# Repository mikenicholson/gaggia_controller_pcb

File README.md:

gaggia_controller_pcb
=====================

A basic PID controller based on the Atmega328p to control my espresso machine.

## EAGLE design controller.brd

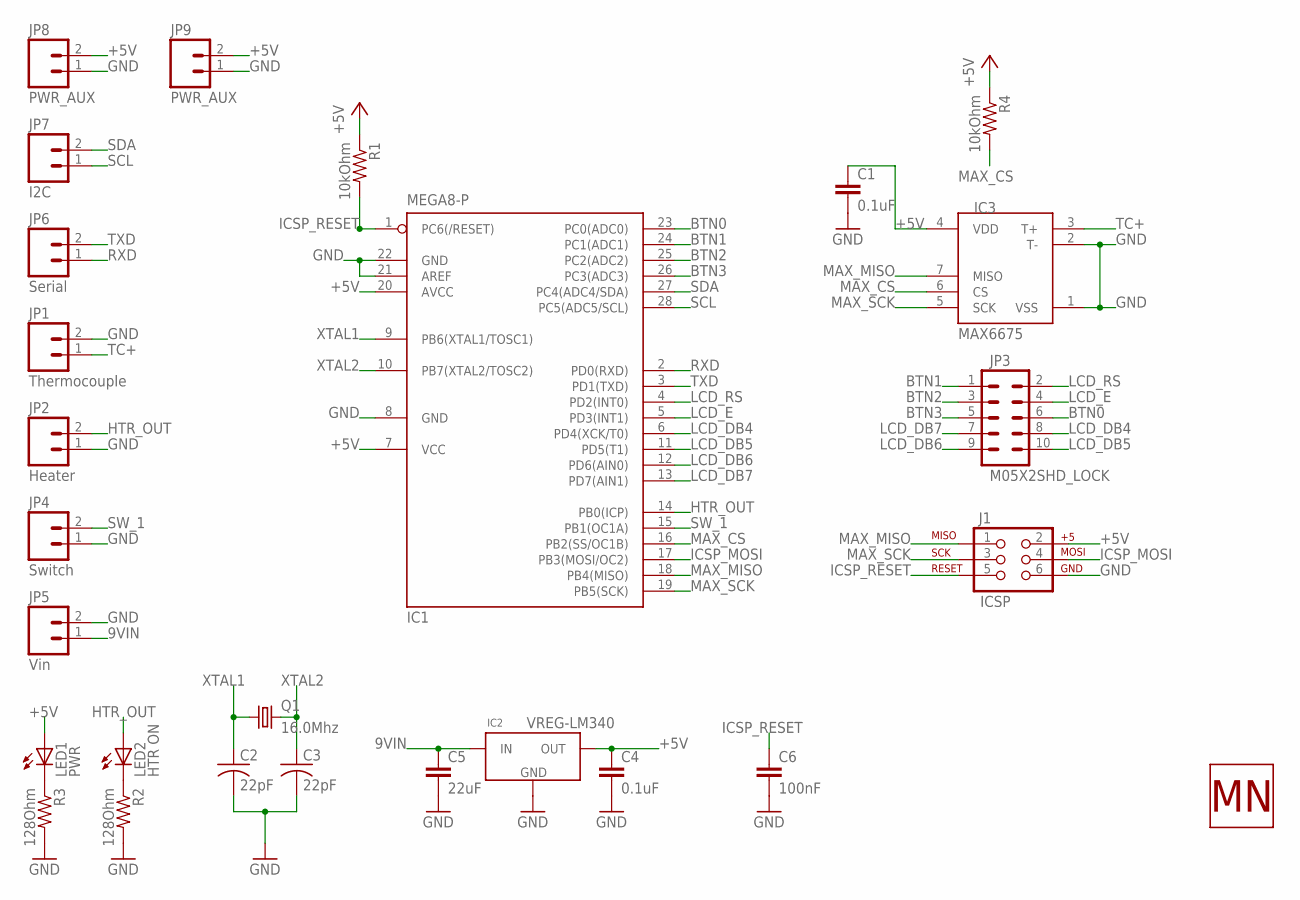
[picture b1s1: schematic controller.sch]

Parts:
C1, C4: 0.1uF; CAP-PTH-SMALL
C2, C3: 22pF; C025-030X050
C5: 22uF; CAP-PTH-5MM
C6: 100nF; 0603-CAP
IC1: MEGA8-P; DIL28-3
IC2: VREG-LM340; D2PACK/A
IC3: MAX6675; SO08-MAX6675
J1: ICSP; 2X3
JP1: Thermocouple; SCREWTERMINAL-5MM-2
JP2: Heater; SCREWTERMINAL-5MM-2
JP3: M05X2SHD_LOCK; 2X5-SHROUDED_LOCK
JP4: Switch; SCREWTERMINAL-5MM-2
JP5: Vin; SCREWTERMINAL-5MM-2
JP6: Serial; 1X02
JP7: I2C; 1X02
JP8: PWR_AUX; 1X02
JP9: PWR_AUX; MOLEX-1X2
LED1: PWR; LED-0603
LED2: HTR ON; LED-0603
Q1: 16.0Mhz; HC49/S
R1, R4: 10kOhm; 1206
R2, R3: 128Ohm; 1206
U$1: MN-LOGO

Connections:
9VIN: C5.1, IC2.1 (IN), JP5.1
+5V: C1.1, C4.1, IC1.7 (VCC), IC1.20 (AVCC), IC2.3 (OUT), IC3.4 (VDD), J1.2, JP8.2, JP9.2, LED1.A, R1.1, R4.1
BTN0: IC1.23 (PC0(ADC0)), JP3.6
BTN1: IC1.24 (PC1(ADC1)), JP3.1
BTN2: IC1.25 (PC2(ADC2)), JP3.3
BTN3: IC1.26 (PC3(ADC3)), JP3.5
GND: C1.2, C2.2, C3.2, C4.2, C5.2, C6.2, IC1.8 (GND), IC1.21 (AREF), IC1.22 (GND), IC2.2 (GND), IC2.TAB (GND), IC3.1 (VSS), IC3.2 (T-), J1.6, JP1.2, JP2.1, JP4.1, JP5.2, JP8.1, JP9.1, R2.2, R3.2
HTR_OUT: IC1.14 (PB0(ICP)), JP2.2, LED2.A
ICSP_MOSI: IC1.17 (PB3(MOSI/OC2)), J1.4
ICSP_RESET: C6.1, IC1.1 (PC6(/RESET)), J1.5, R1.2
LCD_DB4: IC1.6 (PD4(XCK/T0)), JP3.8
LCD_DB5: IC1.11 (PD5(T1)), JP3.10
LCD_DB6: IC1.12 (PD6(AIN0)), JP3.9
LCD_DB7: IC1.13 (PD7(AIN1)), JP3.7
LCD_E: IC1.5 (PD3(INT1)), JP3.4
LCD_RS: IC1.4 (PD2(INT0)), JP3.2
MAX_CS: IC1.16 (PB2(SS/OC1B)), IC3.6 (CS), R4.2
MAX_MISO: IC1.18 (PB4(MISO)), IC3.7 (MISO), J1.1
MAX_SCK: IC1.19 (PB5(SCK)), IC3.5 (SCK), J1.3
unnamed: LED1.C, R3.1
unnamed: LED2.C, R2.1
RXD: IC1.2 (PD0(RXD)), JP6.1
SCL: IC1.28 (PC5(ADC5/SCL)), JP7.1
SDA: IC1.27 (PC4(ADC4/SDA)), JP7.2
SW_1: IC1.15 (PB1(OC1A)), JP4.2
TC+: IC3.3 (T+), JP1.1
TXD: IC1.3 (PD1(TXD)), JP6.2
XTAL1: C2.1, IC1.9 (PB6(XTAL1/TOSC1)), Q1.1
XTAL2: C3.1, IC1.10 (PB7(XTAL2/TOSC2)), Q1.2

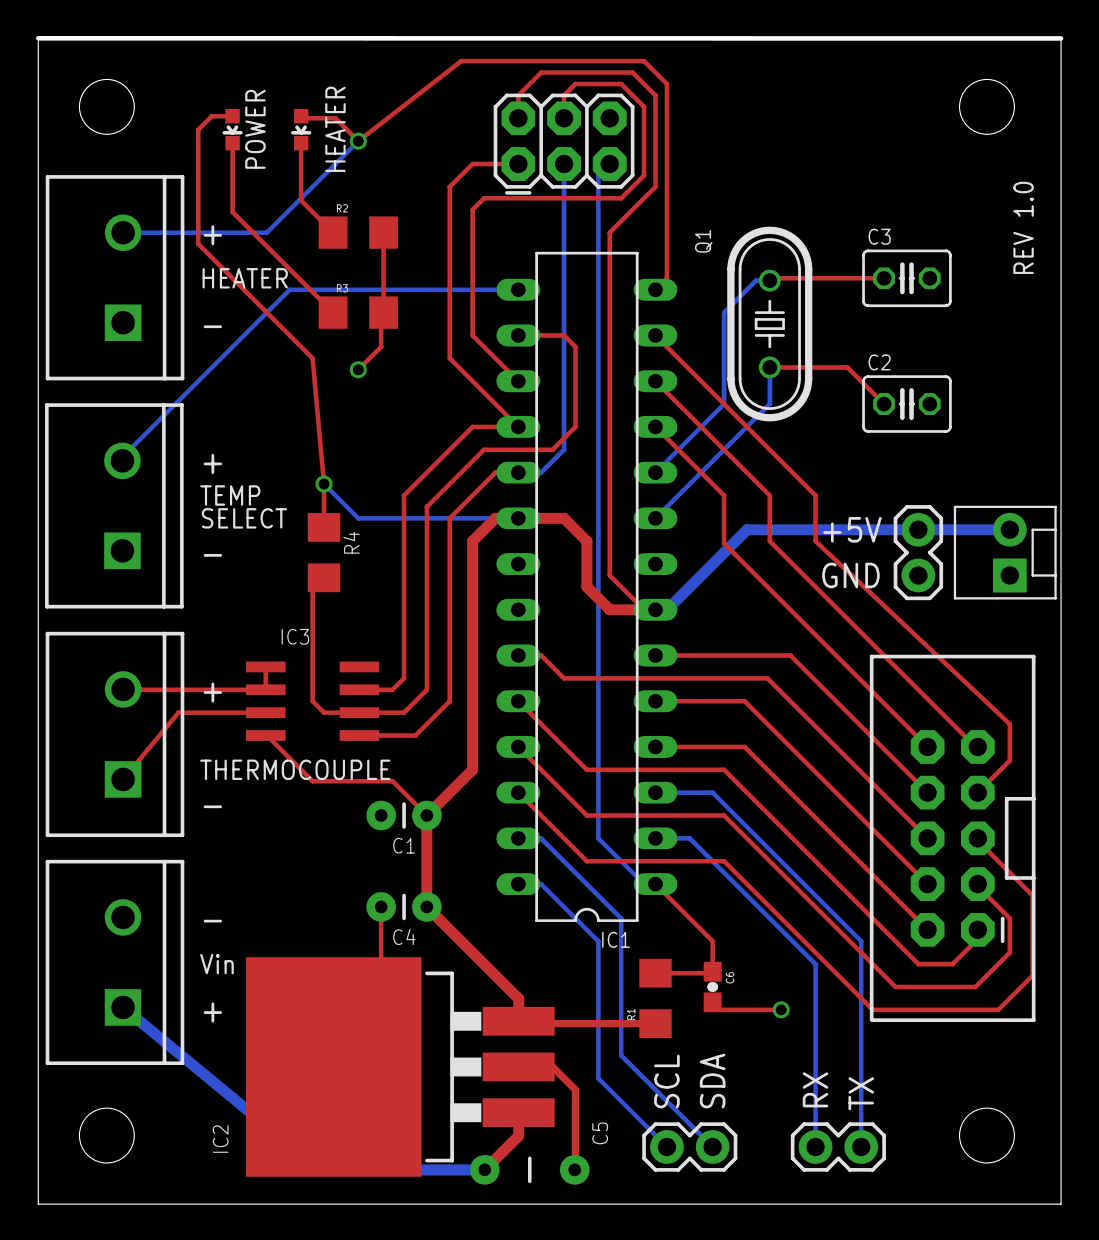
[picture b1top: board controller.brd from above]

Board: 2 copper layers, 56.8 x 64.6 mm, 31 parts (1 on the bottom side), 29 nets.

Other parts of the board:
U$2, U$3, U$4, U$5: STAND-OFF-TIGHT

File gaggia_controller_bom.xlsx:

Description | Value | Name | Schematic | Qty | Supplier | Part No. | Unit Cost | Link
Atmega 8 |  | IC1 | gaggia_controller | 1 | Oh Hand
Vreg-5v | LM340s | IC2 | gaggia_controller | 1 | Digikey | LM340S-5.0/NOPB-ND | 1.66 | buy | Make Symbol/Package in Eagle
MAXX6675 |  | IC3 | gaggia_controller | 1 | Sparkfun | COM-00307 | 11.95 | buy
CRYSTALHC49S | 16.0Mhz | Q1 | gaggia_controller | 1 | On Hand
Capacitor, PTH-Small | 0.1uF | C1,C4 | gaggia_controller | 2 | Sparkfun | PRT-8375 | 0.25 | buy | Power Supply, Not in Schematic
Capacitor, PTH-Small | 22pF | C2-C3 | gaggia_controller | 2 | Sparkfun | COM-08571 | 0.25 | buy
Capacitor, PTH-Small Ceramic Disk | 22uF | C5 | gaggia_controller |  | Digikey | 445-8475-ND | 1.71 | buy
Capacitor | 100nF | C6 | gaggia_controller |  | Sparkfun | PRT-11245 | 0.03 | buy
Resistor, SMD-1206 | 10kOhm, 1/4 Watt | R1,R4 | gaggia_controller | 1 | On Hand
Screw Terminal 5.0mm -2 |  | JP1, JP2,JP4, JP5 | gaggia_controller | 4 | Sparkfun | PRT-08432 | 0.95 | buy
Shrouded Header 2x5 |  | JP3 | gaggia_controller | 1 | Sparkfun | PRT-08506 | 1.5 | buy
ICSP Header | 6-PTH | J1 | gaggia_controller | 1 | On Hand
Resistor, SMD-1206 | 128 Ohm | R2, R3 | gaggia_controller | 2 | Digikey | P130FCT-ND | 0.1 | buy
LED, SMD-0603 | Green | LED1 | gaggia_controller | 1 | Sparkfun | PRT-11249 | 0.2 | buy
LED, SMD-0603 | Red | LED2 | gaggia_controller | 1 | Sparkfun | PRT-11248 | 0.24 | buy
16x2 LCD |  | U1 | Interface_panel | 1
Ribbon Cable - 10 Conductor | 15ft |  | Connector Cable |  | Sparkfun | CAB-10647
Keyed Header, Femal |  |  | Connector Cable | 2 | Digikey

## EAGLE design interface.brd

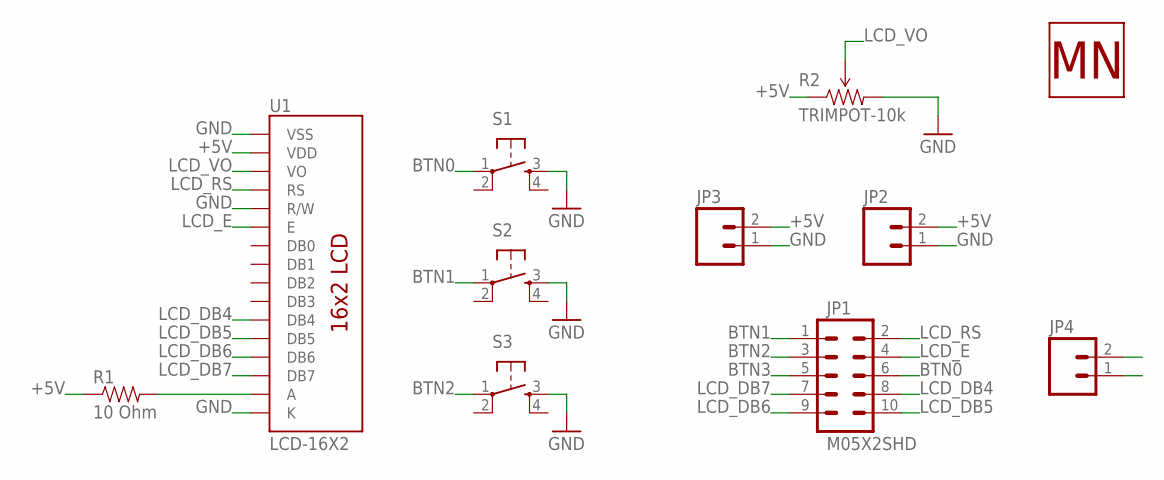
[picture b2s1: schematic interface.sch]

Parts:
JP1: M05X2SHD; 2X5-SHROUDED
JP2: M02POLAR; MOLEX-1X2
JP3, JP4: M02PTH; 1X02
R1: 10 Ohm; 1206
R2: TRIMPOT-10k; TRIMPOT_TC33
S1, S2, S3: TAC_SWITCHPTH; TACTILE-PTH
U1: LCD-16X2; LCD-16X2_NOLEFTDRILL
U$5: MN-LOGO

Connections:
+5V: JP2.2, JP3.2, R1.1, R2.1 (CCW), U1.2 (VDD)
BTN0: JP1.6, S1.1
BTN1: JP1.1, S2.1
BTN2: JP1.3, S3.1
BTN3: JP1.5, JP4.2
GND: JP2.1, JP3.1, JP4.1, R2.3 (CW), S1.3, S2.3, S3.3, U1.1 (VSS), U1.5 (R/W), U1.16 (K)
LCD_DB4: JP1.8, U1.11 (DB4)
LCD_DB5: JP1.10, U1.12 (DB5)
LCD_DB6: JP1.9, U1.13 (DB6)
LCD_DB7: JP1.7, U1.14 (DB7)
LCD_E: JP1.4, U1.6 (E)
LCD_RS: JP1.2, U1.4 (RS)
LCD_VO: R2.2 (WIPER), U1.3 (VO)
unnamed: R1.2, U1.15 (A)

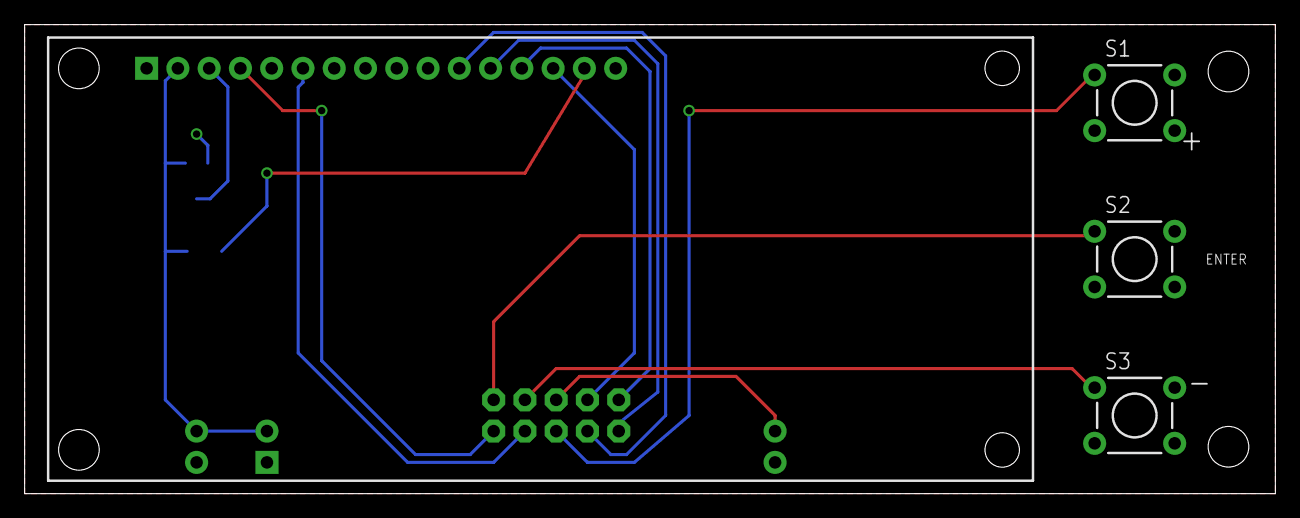
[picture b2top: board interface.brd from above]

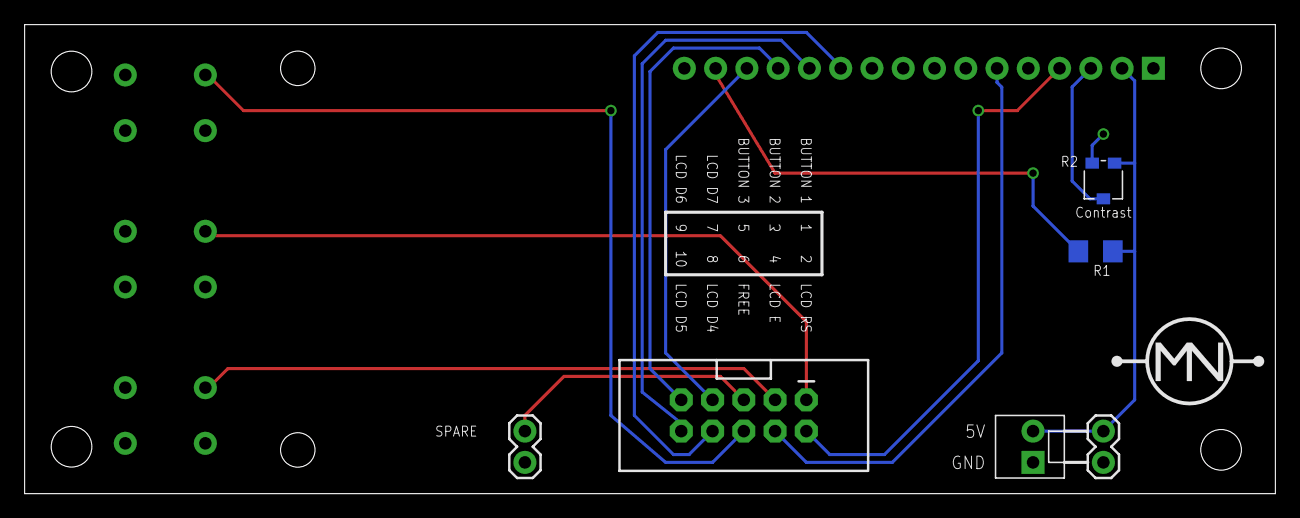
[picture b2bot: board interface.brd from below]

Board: 2 copper layers, 101.6 x 38.1 mm, 15 parts (7 on the bottom side), 14 nets.

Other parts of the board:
U$1, U$2, U$3, U$4: STAND-OFF

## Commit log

2012-12-09 Initial checkin of all files.
2012-12-09 Adding git ignore. Don't track automatically create backups
2012-12-09 Renamed files to allow for creating interface board.
2012-12-10 Added schematic and layout for interface file.
2012-12-10 Removed extraneous silkscreen
2012-12-11 Added silk screen documentation for 10 pin connector
2012-12-11 Cleaning up DRC issues
    Sparkfun package TRIMPOT_TC33 had issues with silkscreen. SS from LCD was passing over some pads. Switched LCD ss to tDocu and cleaned up ss lines on trimpot so they no longer overlapped the pads.
2012-12-11 Added header for spare pin from 10pin connector.
    Added a 2pin header to allow access to the "spare" pin on the 10 pin
    header.
2012-12-12 Fixed orientation of screw terminals.
    Screw terminals were oriented with receptacle facing inwards towards
    the center of the board. Rotated them and performed some pin swaps.
    Also added silk to label contrast trim pot on interface board.
2012-12-13 Changed 1 of the aux power connectors to molex polarized header.
    Made change for interface and for controller boards
2012-12-30 Silkscreen cleanup and terminal moves.
    Silkscreen was overlapping the pad for Heater LED's
    current limiting resitor. Also spaced out screw terminals.
    Prevents them from meshing but allows for use of different near
    -equivalent parts.
2013-01-06 Updated some layout, added logo

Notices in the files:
parts and their libraries:
SparkFun-AnalogIC: Licensing: CC v3.0 Share-Alike You are welcome to use this library for commercial purposes.
